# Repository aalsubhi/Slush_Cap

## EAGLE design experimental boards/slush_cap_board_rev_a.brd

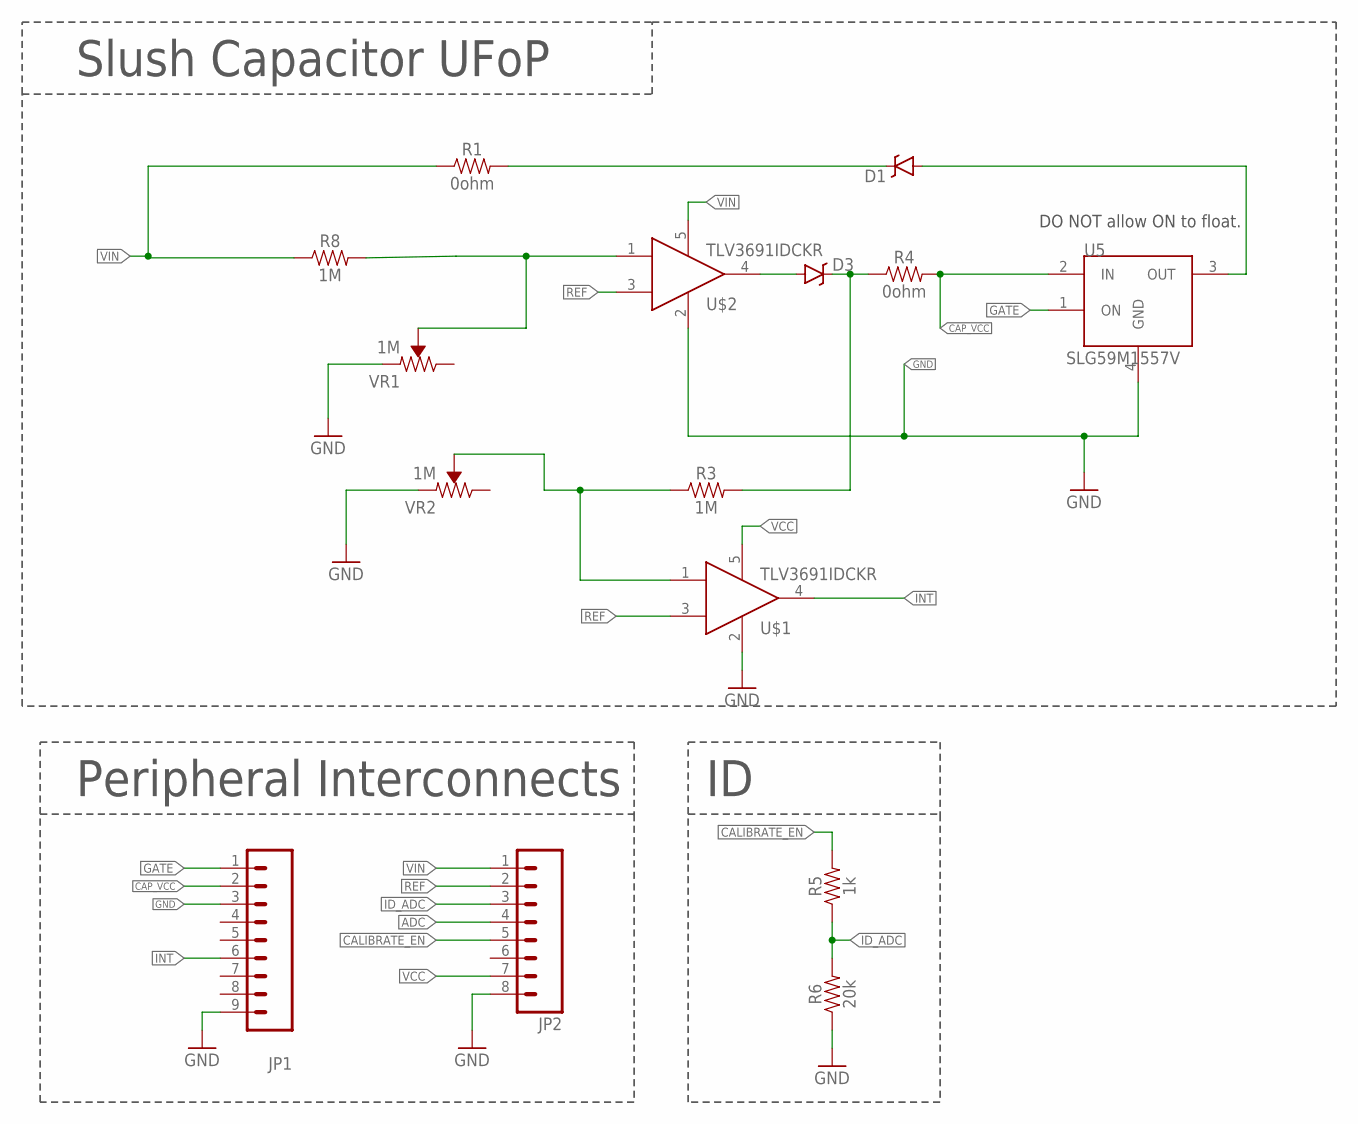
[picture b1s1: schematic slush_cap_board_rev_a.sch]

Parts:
D1, D3: RB751; SOD-523; MPN BAS40-02V-V-G-08; DIGIKEY BAS40-02V-V-G-08GICT-ND
JP1: M091.27MM; 1X09-1.27MM; MANUFACTURERPARTNUMBER GRPB091VWVN-RC; DIGIKEY S9014E-09-ND
JP2: M081.27MM; 1X08-1.27MM; MANUFACTURERPARTNUMBER GRPB081VWVN-RC; DIGIKEY S9014E-08-ND
R1, R4: 0ohm; 0603
R3, R8: 1M; 0805
R5: 1k; 0603
R6: 20k; 0603
U5: SLG59M1557V; 4STDFN; MPN SLG59M1557V; MOUSER 402-SLG59M1557V
U$1, U$2: TLV3691IDCKR; SOT353
VR1, VR2: 1M; TRIMPOT-SMD-3MM-CLOSED

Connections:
ADC: JP2.4
CALIBRATE_EN: JP2.5, R5.2
CAP_VCC: JP1.2, R4.2, U5.2 (IN)
GATE: JP1.1, U5.1 (ON)
GND: JP1.3, JP1.9, JP2.8, R6.1, U5.4 (GND), U$1.2, U$2.2, VR1.1 (CCW), VR2.1 (CCW)
ID_ADC: JP2.3, R5.1, R6.2
INT: JP1.6, U$1.4
unnamed: D3.A, U$2.4
unnamed: D3.C, R3.2, R4.1
unnamed: D1.A, U5.3 (OUT)
unnamed: R8.2, U$2.1, VR1.2 (WIPER)
unnamed: R3.1, U$1.1, VR2.2 (WIPER)
unnamed: D1.C, R1.2
REF: JP2.2, U$1.3, U$2.3
VCC: JP2.7, U$1.5
VIN: JP2.1, R1.1, R8.1, U$2.5

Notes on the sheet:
DO NOT allow ON to float.
Peripheral Interconnects
Slush Capacitor UFoP

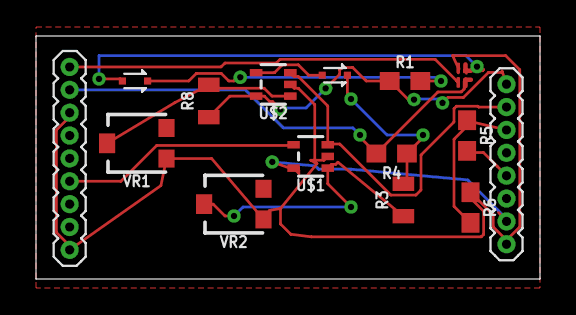
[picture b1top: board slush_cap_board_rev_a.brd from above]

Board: 2 copper layers, 28.0 x 13.5 mm, 15 parts (0 on the bottom side), 15 nets.

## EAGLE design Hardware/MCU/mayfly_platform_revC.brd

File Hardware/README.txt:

hardwareCtrl: Currently I'm using the hardware control version of the slush cap.

peripheral_platform: has the design of all peripherals that used in slush cap experiment such as radio, one analog sensor, and two analog sensors.

MCU: has Flicker board design with the extra standard headers.

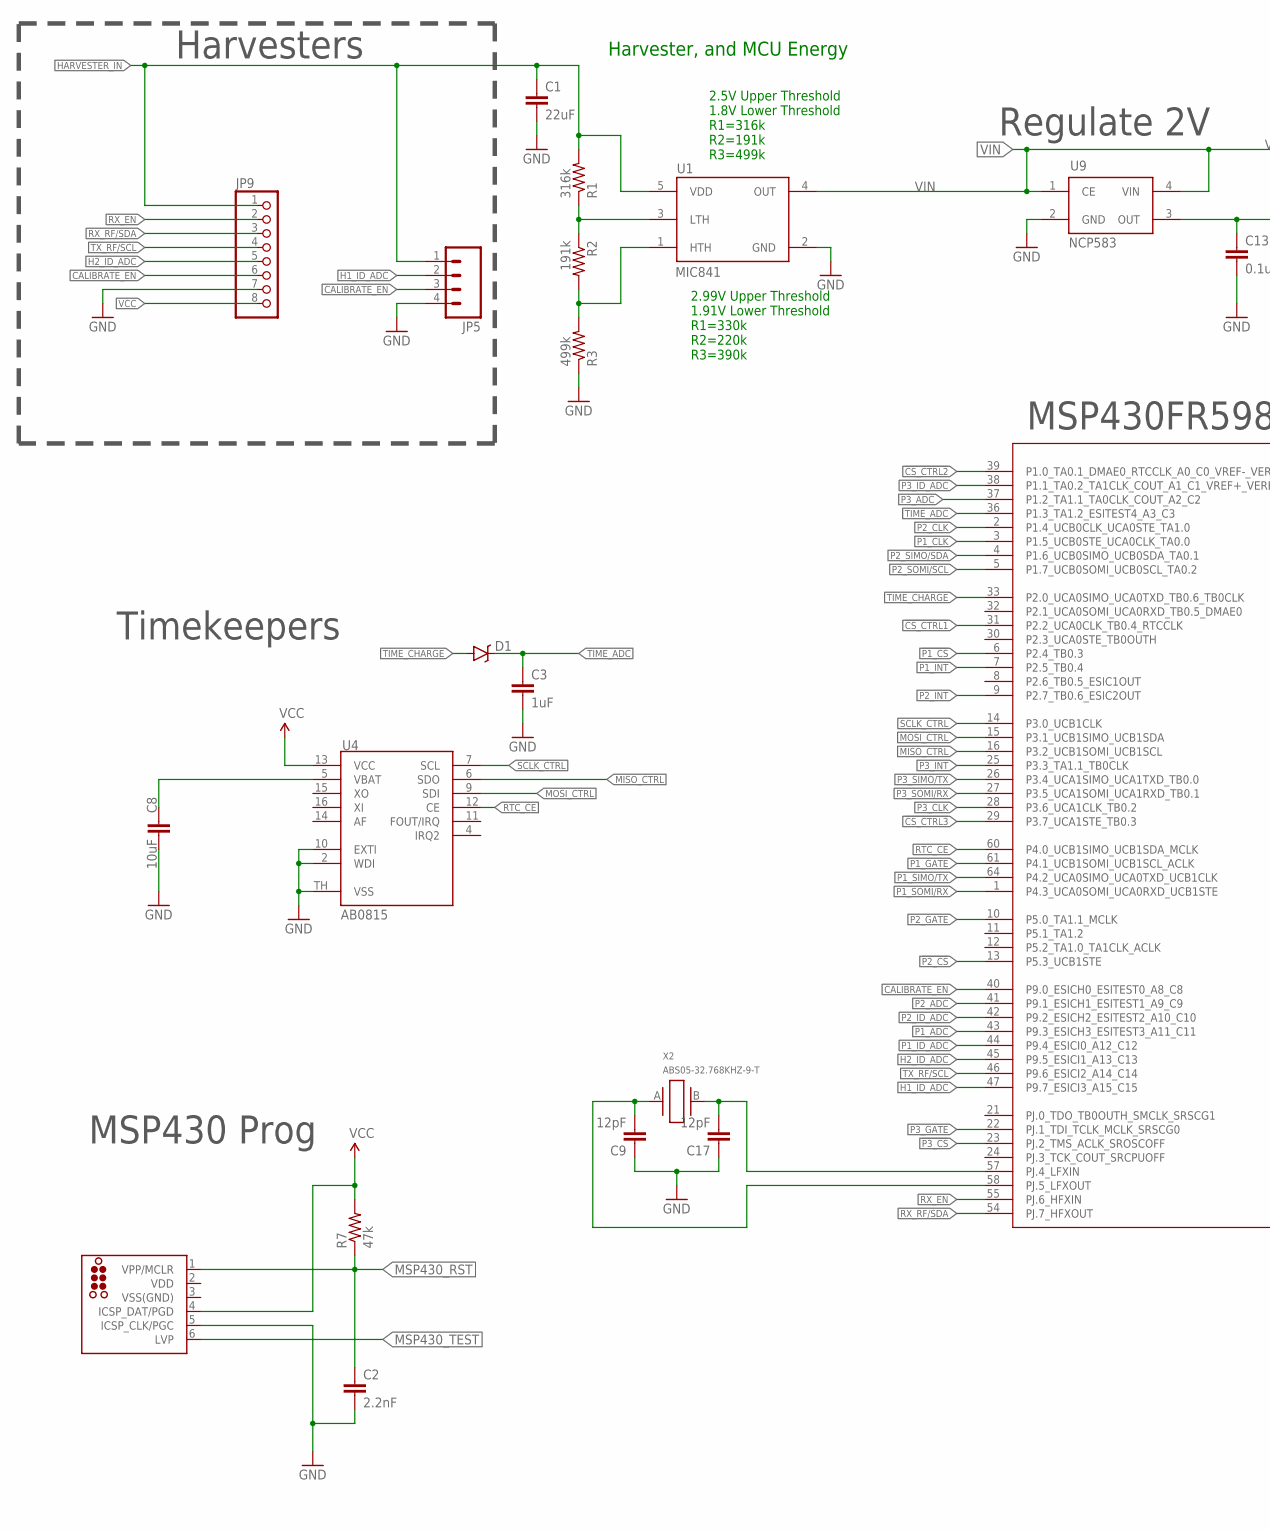
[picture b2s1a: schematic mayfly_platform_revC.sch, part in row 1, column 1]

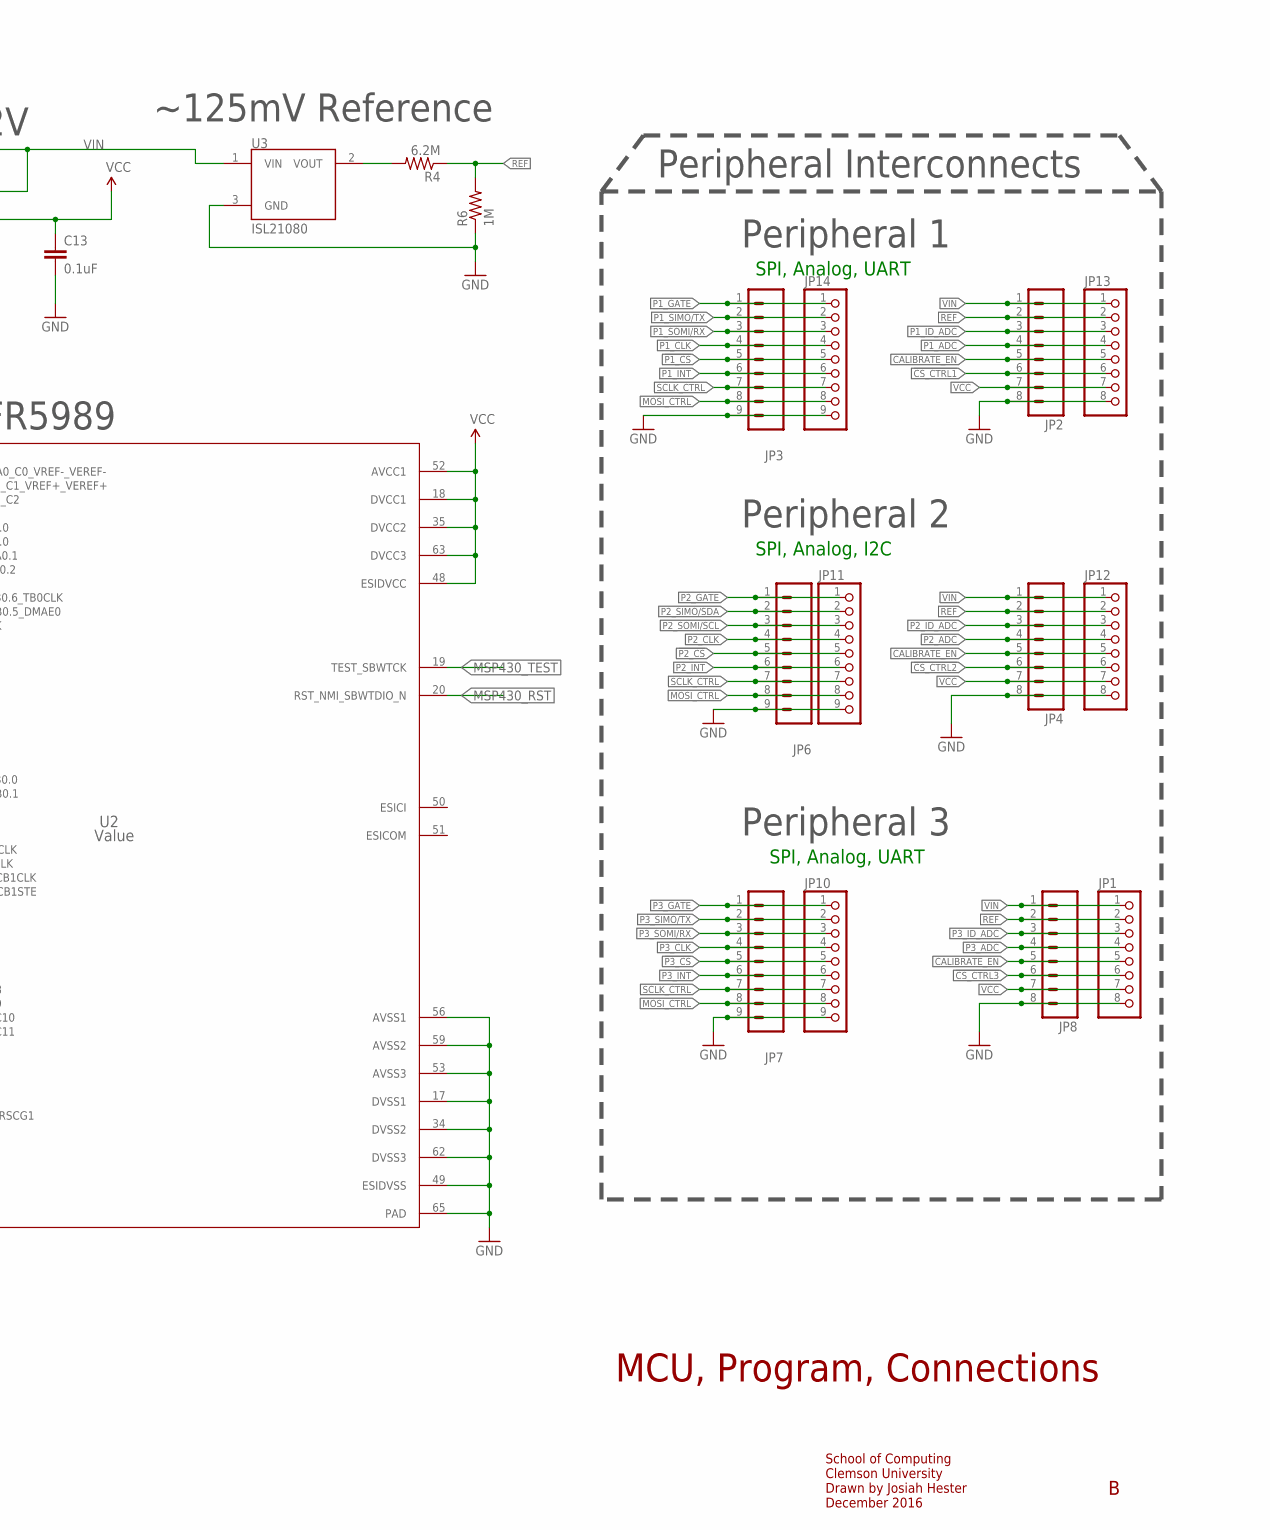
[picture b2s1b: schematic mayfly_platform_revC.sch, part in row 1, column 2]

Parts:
C1: 22uF; 1210; MANUFACTURERPARTNUMBER CL32A226KAJNNNE
C2: 2.2nF; 0603; MPN 06035C222KAT2A
C3: 1uF; 0603; MANUFACTURERPARTNUMBER 0603YD105KAT2A
C8: 10uF; 0805; MPN 0805YD106KAT2A
C9, C17: 12pF; 0603; MPN CL10C120JB8NNNC
C13: 0.1uF; 0603; MANUFACTURERPARTNUMBER 0603YC104KAT2A
D1: RB751; SOD-523; MPN BAS40-02V-V-G-08; DIGIKEY BAS40-02V-V-G-08GICT-ND
J1: TC2030-MCP-NL
JP1, JP9, JP12, JP13: PINHD-1X8; 1X08
JP2, JP4, JP8: M081.27MM; 1X08-1.27MM; MPN 851-43-008-10-001000; DIGIKEY ED90570-ND
JP3, JP6, JP7: M091.27MM; 1X09-1.27MM; MPN 851-87-009-10-001101; DIGIKEY 1212-1354-ND
JP5: M041.27MM; 1X04-1.27MM; MANUFACTURERPARTNUMBER 851-43-004-10-001000; DIGIKEY ED90528-ND
JP10, JP11, JP14: PINHD-1X9; 1X09
R1: 316k; 0603; MANUFACTURERPARTNUMBER RC0603FR-07316KL; DIGIKEY 311-316KHRCT-ND
R2: 191k; 0603; MANUFACTURERPARTNUMBER RC0603FR-07191KL; DIGIKEY 311-191KHRCT-ND
R3: 499k; 0603; MANUFACTURERPARTNUMBER RC0603FR-07499KL; DIGIKEY 311-499KHRCT-ND
R4: 6.2M; 0603; MPN CRCW06036M20FKEA; DIGIKEY 541-6.20MHCT-ND
R6: 1M; 0603; MPN RC0603FR-071ML; DIGIKEY 311-1.00MHRCT-ND
R7: 47k; 0603; MPN CRCW060347K0JNEA
U1: MIC841; SC70-5; MPN MIC841HYC5-TR; DIGIKEY 576-2923-1-ND
U2: Value; RGC0064B; MPN MSP430FR59891IRGCT; DIGIKEY 296-42031-1-ND
U3: ISL21080; SOT-23; MPN ISL21080DIH309Z-TK; DIGIKEY ISL21080DIH309Z-TKCT-ND
U4: AB0815; QFN16; MPN AB0815-T3
U9: NCP583; SC82-AB_1PRIMARY; MPN NCP583SQ18T1G; DIGIKEY NCP583SQ18T1GOSCT-ND
X2: ABS05-32.768KHZ-9-T; ABS05; MPN ABS05-32.768KHZ-9-T

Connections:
!CS_CTRL1: JP2.6, JP13.6, U2.31 (P2.2_UCA0CLK_TB0.4_RTCCLK)
!CS_CTRL2: JP4.6, JP12.6, U2.39 (P1.0_TA0.1_DMAE0_RTCCLK_A0_C0_VREF-_VER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)
!CS_CTRL3: JP1.6, JP8.6, U2.29 (P3.7_UCA1STE_TB0.3)
!P1_CS: JP3.5, JP14.5, U2.6 (P2.4_TB0.3)
!P2_CS: JP6.5, JP11.5, U2.13 (P5.3_UCB1STE)
!P3_CS: JP7.5, JP10.5, U2.23 (PJ.2_TMS_ACLK_SROSCOFF)
CALIBRATE_EN: JP1.5, JP2.5, JP4.5, JP5.3, JP8.5, JP9.6, JP12.5, JP13.5, U2.40 (P9.0_ESICH0_ESITEST0_A8_C8)
GND: C1.2, C2.2, C3.2, C8.2, C9.1, C13.2, C17.1, J1.5 (ICSP_CLK/PGC), JP1.8, JP2.8, JP3.9, JP4.8, JP5.4, JP6.9, JP7.9, JP8.8, JP9.7, JP10.9, JP11.9, JP12.8, JP13.8, JP14.9, R3.1, R6.1, U1.2 (GND), U2.17 (DVSS1), U2.34 (DVSS2), U2.49 (ESIDVSS), U2.53 (AVSS3), U2.56 (AVSS1), U2.59 (AVSS2), U2.62 (DVSS3), U2.65 (PAD), U3.3 (GND), U4.2 (WDI), U4.10 (EXTI), U4.TH (VSS), U9.2 (GND)
H1_ID_ADC: JP5.2, U2.47 (P9.7_ESICI3_A15_C15)
H2_ID_ADC: JP9.5, U2.45 (P9.5_ESICI1_A13_C13)
HARVESTER_IN: C1.1, JP5.1, JP9.1, R1.2, U1.5 (VDD)
MISO_CTRL: U2.16 (P3.2_UCB1SOMI_UCB1SCL), U4.6 (SDO)
MOSI_CTRL: JP3.8, JP6.8, JP7.8, JP10.8, JP11.8, JP14.8, U2.15 (P3.1_UCB1SIMO_UCB1SDA), U4.9 (SDI)
MSP430_RST: C2.1, J1.1 (VPP/MCLR), R7.1, U2.20 (RST_NMI_SBWTDIO_N)
MSP430_TEST: J1.6 (LVP), U2.19 (TEST_SBWTCK)
unnamed: R1.1, R2.1, U1.3 (LTH)
unnamed: R4.2, U3.2 (VOUT)
unnamed: R2.2, R3.2, U1.1 (HTH)
unnamed: C17.2, U2.57 (PJ.4_LFXIN), X2.B (2)
unnamed: C9.2, U2.58 (PJ.5_LFXOUT), X2.A (1)
unnamed: C8.1, U4.5 (VBAT)
P1_ADC: JP2.4, JP13.4, U2.43 (P9.3_ESICH3_ESITEST3_A11_C11)
P1_CLK: JP3.4, JP14.4, U2.3 (P1.5_UCB0STE_UCA0CLK_TA0.0)
P1_GATE: JP3.1, JP14.1, U2.61 (P4.1_UCB1SOMI_UCB1SCL_ACLK)
P1_ID_ADC: JP2.3, JP13.3, U2.44 (P9.4_ESICI0_A12_C12)
P1_INT: JP3.6, JP14.6, U2.7 (P2.5_TB0.4)
P1_SIMO/TX: JP3.2, JP14.2, U2.64 (P4.2_UCA0SIMO_UCA0TXD_UCB1CLK)
P1_SOMI/RX: JP3.3, JP14.3, U2.1 (P4.3_UCA0SOMI_UCA0RXD_UCB1STE)
P2_ADC: JP4.4, JP12.4, U2.41 (P9.1_ESICH1_ESITEST1_A9_C9)
P2_CLK: JP6.4, JP11.4, U2.2 (P1.4_UCB0CLK_UCA0STE_TA1.0)
P2_GATE: JP6.1, JP11.1, U2.10 (P5.0_TA1.1_MCLK)
P2_ID_ADC: JP4.3, JP12.3, U2.42 (P9.2_ESICH2_ESITEST2_A10_C10)
P2_INT: JP6.6, JP11.6, U2.9 (P2.7_TB0.6_ESIC2OUT)
P2_SIMO/SDA: JP6.2, JP11.2, U2.4 (P1.6_UCB0SIMO_UCB0SDA_TA0.1)
P2_SOMI/SCL: JP6.3, JP11.3, U2.5 (P1.7_UCB0SOMI_UCB0SCL_TA0.2)
P3_ADC: JP1.4, JP8.4, U2.37 (P1.2_TA1.1_TA0CLK_COUT_A2_C2)
P3_CLK: JP7.4, JP10.4, U2.28 (P3.6_UCA1CLK_TB0.2)
P3_GATE: JP7.1, JP10.1, U2.22 (PJ.1_TDI_TCLK_MCLK_SRSCG0)
P3_ID_ADC: JP1.3, JP8.3, U2.38 (P1.1_TA0.2_TA1CLK_COUT_A1_C1_VREF+_VERE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)
P3_INT: JP7.6, JP10.6, U2.25 (P3.3_TA1.1_TB0CLK)
P3_SIMO/TX: JP7.2, JP10.2, U2.26 (P3.4_UCA1SIMO_UCA1TXD_TB0.0)
P3_SOMI/RX: JP7.3, JP10.3, U2.27 (P3.5_UCA1SOMI_UCA1RXD_TB0.1)
REF: JP1.2, JP2.2, JP4.2, JP8.2, JP12.2, JP13.2, R4.1, R6.2
RTC_CE: U2.60 (P4.0_UCB1SIMO_UCB1SDA_MCLK), U4.12 (CE)
RX_EN: JP9.2, U2.55 (PJ.6_HFXIN)
RX_RF/SDA: JP9.3, U2.54 (PJ.7_HFXOUT)
SCLK_CTRL: JP3.7, JP6.7, JP7.7, JP10.7, JP11.7, JP14.7, U2.14 (P3.0_UCB1CLK), U4.7 (SCL)
TIME_ADC: C3.1, D1.C, U2.36 (P1.3_TA1.2_ESITEST4_A3_C3)
TIME_CHARGE: D1.A, U2.33 (P2.0_UCA0SIMO_UCA0TXD_TB0.6_TB0CLK)
TX_RF/SCL: JP9.4, U2.46 (P9.6_ESICI2_A14_C14)
VCC: C13.1, J1.4 (ICSP_DAT/PGD), JP1.7, JP2.7, JP4.7, JP8.7, JP9.8, JP12.7, JP13.7, R7.2, U2.18 (DVCC1), U2.35 (DVCC2), U2.48 (ESIDVCC), U2.52 (AVCC1), U2.63 (DVCC3), U4.13 (VCC), U9.3 (OUT)
VDD: J1.2 (VDD)
VIN: JP1.1, JP2.1, JP4.1, JP8.1, JP12.1, JP13.1, U1.4 (OUT), U3.1 (VIN), U9.1 (CE), U9.4 (VIN)
VSS(GND): J1.3 (VSS(GND))

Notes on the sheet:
MCU, Program, Connections
School of Computing Clemson University Drawn by Josiah Hester December 2016
MSP430FR5989
Regulate 2V
MSP430 Prog
Timekeepers
2.99V Upper Threshold 1.91V Lower Threshold R1=330k R2=220k R3=390k
Harvester, and MCU Energy
~125mV Reference
Peripheral 1
Peripheral 2
Peripheral 3
Harvesters
SPI, Analog, I2C
SPI, Analog, UART
Peripheral Interconnects
2.5V Upper Threshold 1.8V Lower Threshold R1=316k R2=191k R3=499k

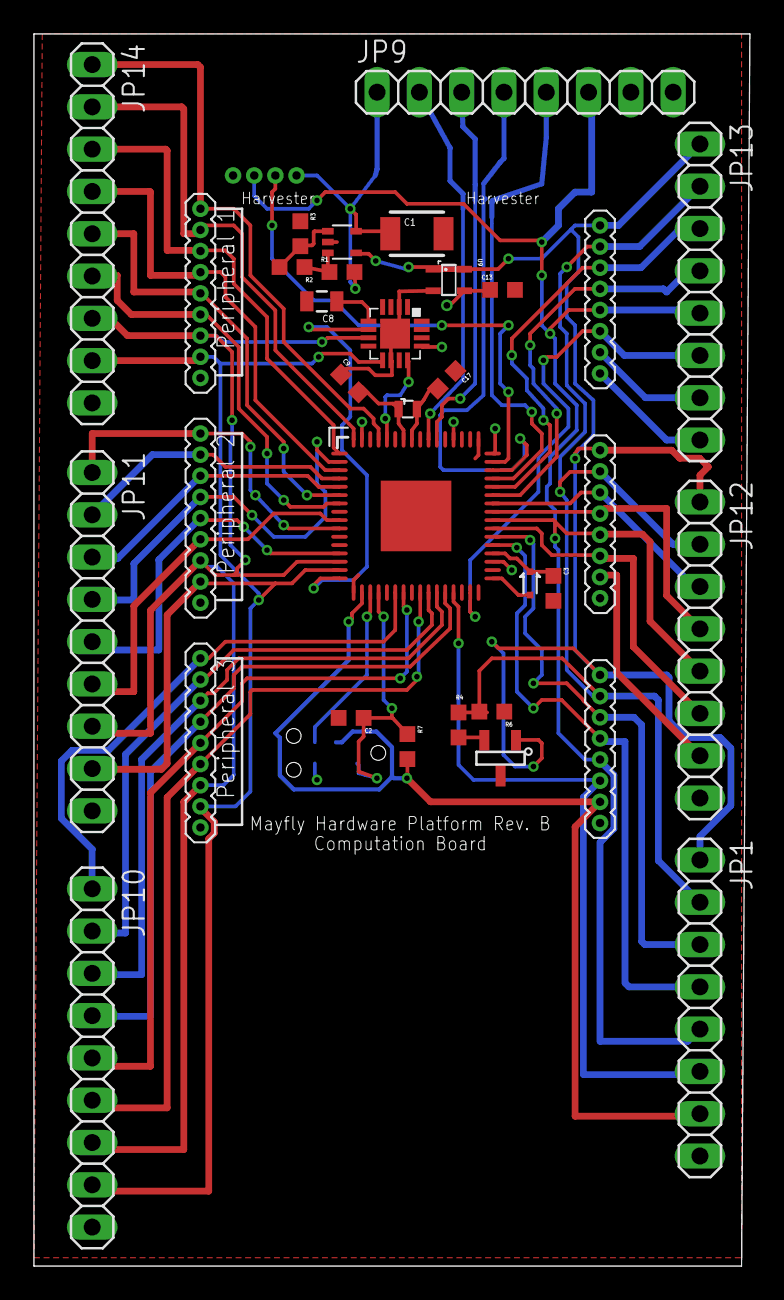
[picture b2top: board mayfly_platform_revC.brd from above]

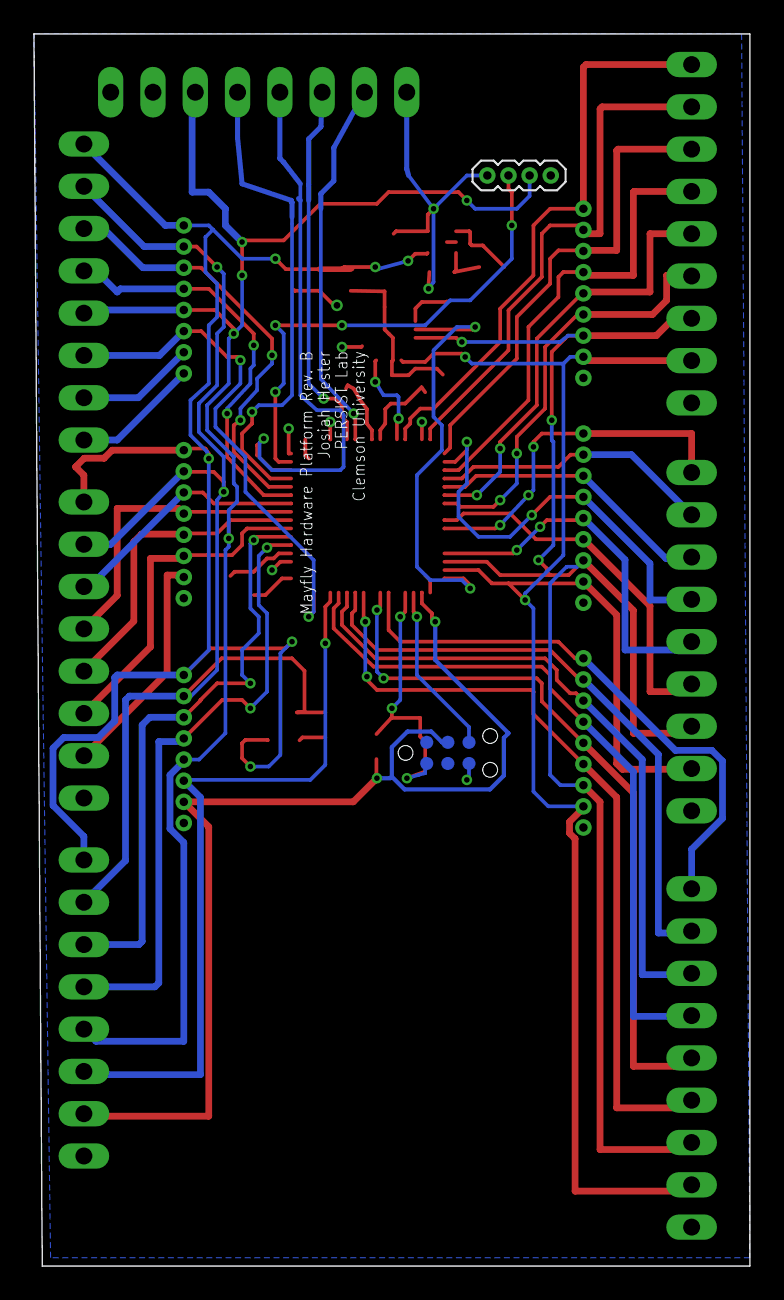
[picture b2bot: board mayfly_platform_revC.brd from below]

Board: 2 copper layers, 43.0 x 74.0 mm, 35 parts (2 on the bottom side), 52 nets.

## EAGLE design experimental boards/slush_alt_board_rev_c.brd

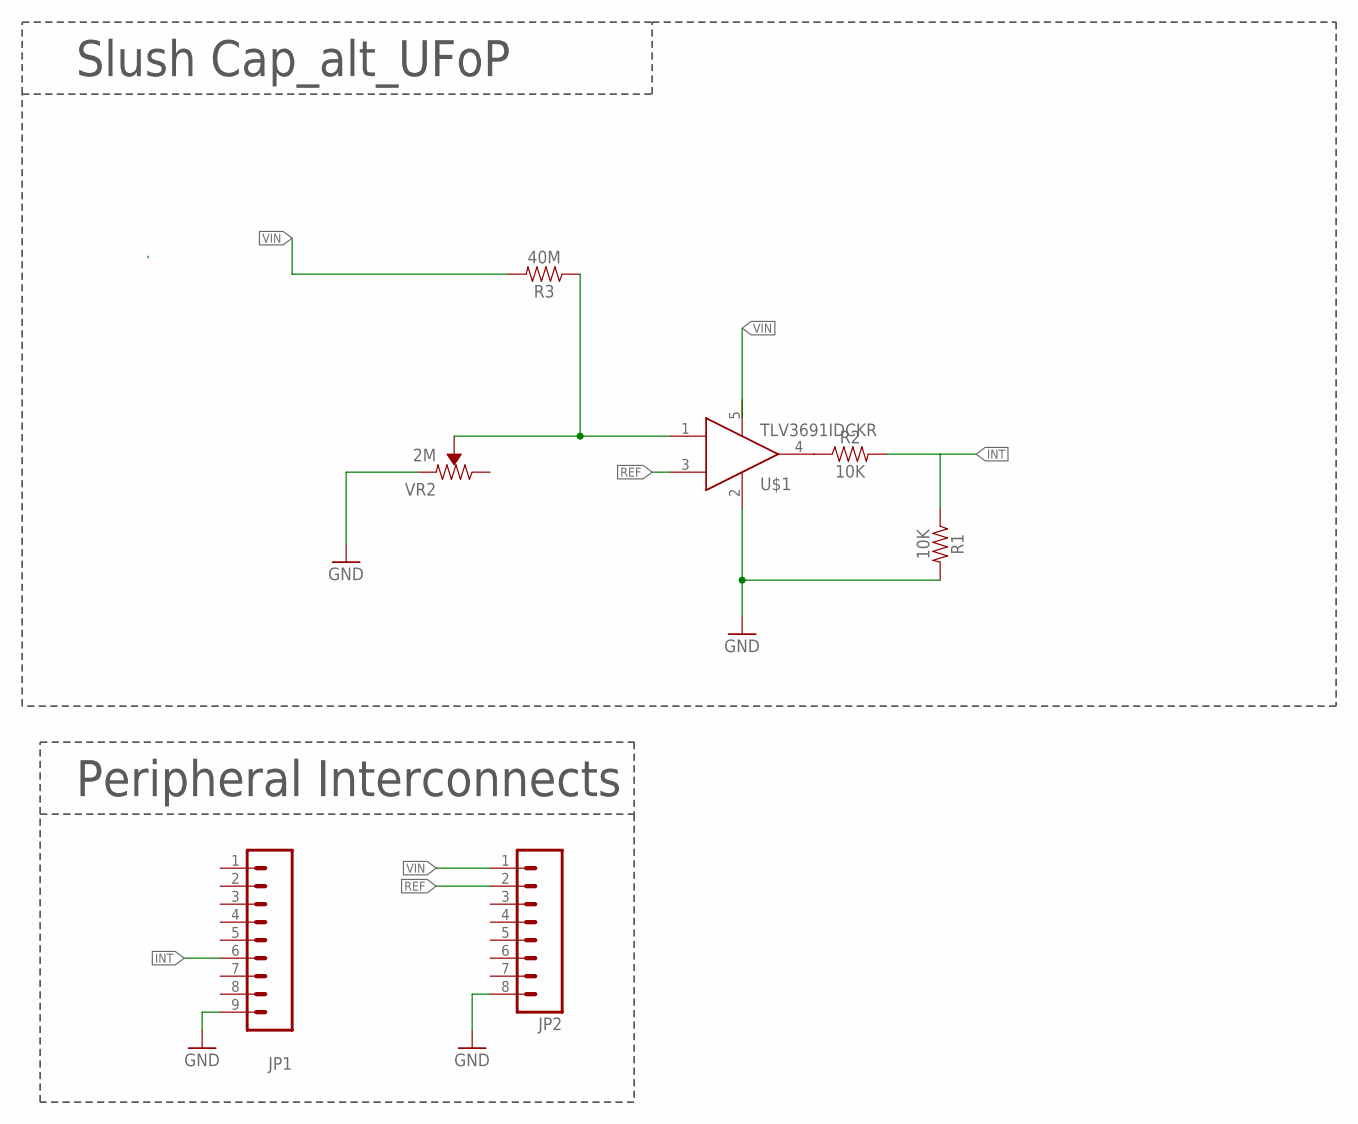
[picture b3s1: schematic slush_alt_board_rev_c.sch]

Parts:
JP1: M091.27MM; 1X09-1.27MM; MANUFACTURERPARTNUMBER GRPB091VWVN-RC; DIGIKEY S9014E-09-ND
JP2: M081.27MM; 1X08-1.27MM; MANUFACTURERPARTNUMBER GRPB081VWVN-RC; DIGIKEY S9014E-08-ND
R1, R2: 10K; 0805
R3: 40M; 0805
U$1: TLV3691IDCKR; SOT353
VR2: 2M; TRIMPOT-SMD-3MM-CLOSED

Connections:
GND: JP1.9, JP2.8, R1.2, U$1.2, VR2.1 (CCW)
INT: JP1.6, R1.1, R2.2
unnamed: R2.1, U$1.4
unnamed: R3.1, U$1.1, VR2.2 (WIPER)
REF: JP2.2, U$1.3
VIN: JP2.1, R3.2, U$1.5

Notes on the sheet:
Peripheral Interconnects
Slush Cap_alt_UFoP

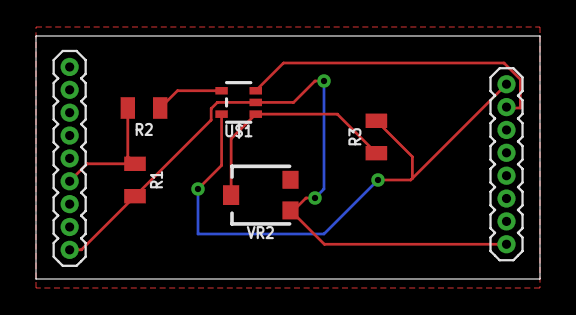
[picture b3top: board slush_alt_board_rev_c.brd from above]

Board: 2 copper layers, 28.0 x 13.5 mm, 7 parts (0 on the bottom side), 6 nets.

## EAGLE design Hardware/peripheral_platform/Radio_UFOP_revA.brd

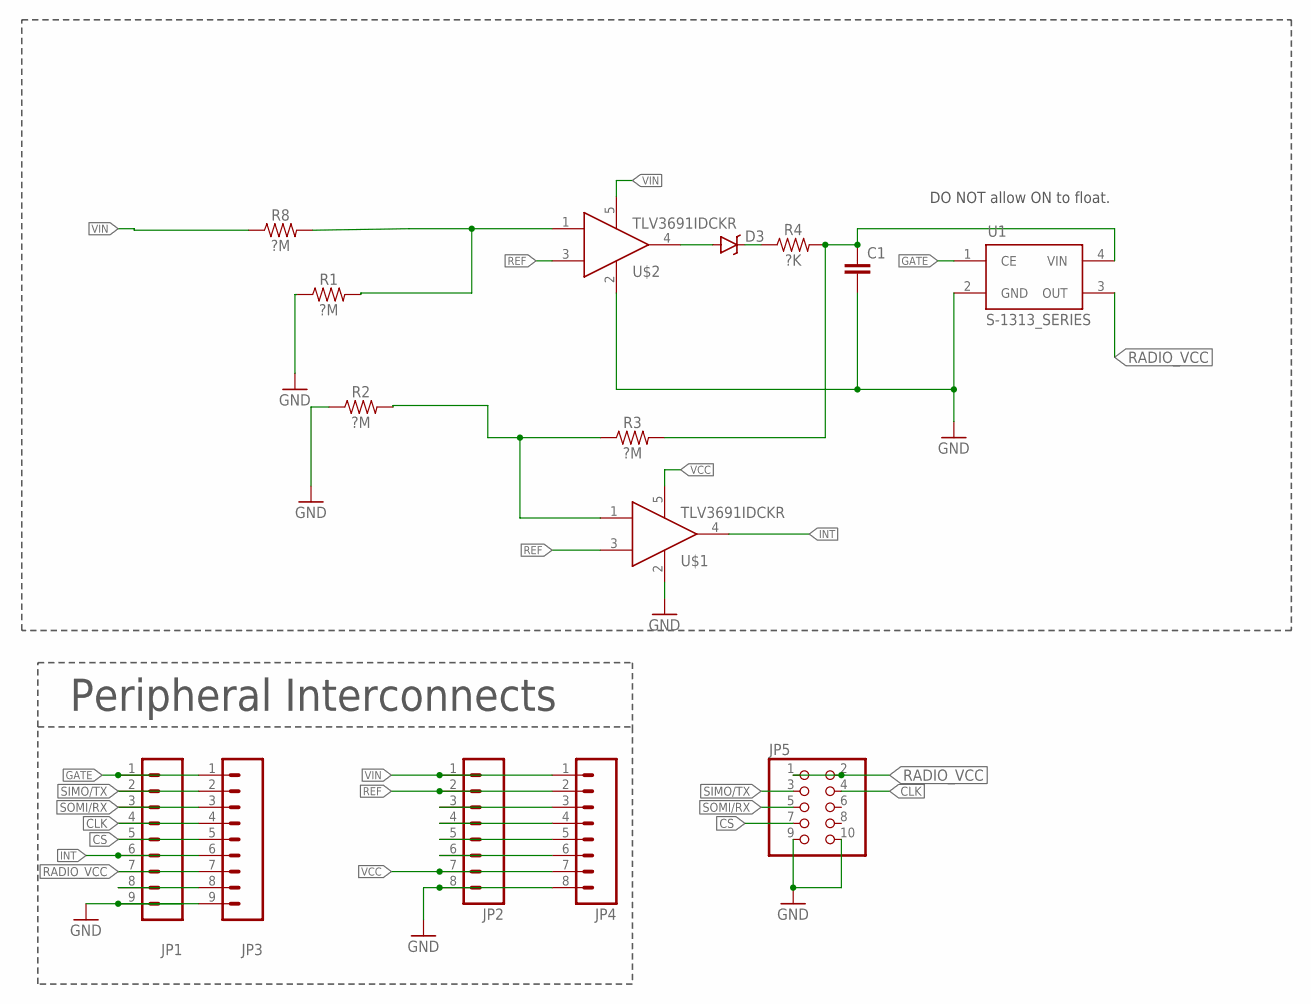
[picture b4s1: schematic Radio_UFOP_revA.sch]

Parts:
C1: CAP0603-CAP; 0603-CAP
D3: RB751; SOD-523; MPN BAS40-02V-V-G-08; DIGIKEY BAS40-02V-V-G-08GICT-ND
JP1, JP3: M091.27MM; 1X09-1.27MM; MANUFACTURERPARTNUMBER GRPB091VWVN-RC; DIGIKEY S9014E-09-ND
JP2, JP4: M081.27MM; 1X08-1.27MM; MANUFACTURERPARTNUMBER GRPB081VWVN-RC; DIGIKEY S9014E-08-ND
JP5: PINHD-2X5; 2X05
R1, R2, R3, R8: ?M; 0805
R4: ?K; 0805
U1: S-1313_SERIES; SC82-AB_1PRIMARY
U$1, U$2: TLV3691IDCKR; SOT353

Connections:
CLK: JP1.4, JP3.4, JP5.4
CS: JP1.5, JP3.5, JP5.7
GATE: JP1.1, JP3.1, U1.1 (CE)
GND: C1.2, JP1.9, JP2.8, JP3.9, JP4.8, JP5.9, JP5.10, R1.1, R2.1, U1.2 (GND), U$1.2, U$2.2
INT: JP1.6, JP3.6, U$1.4
unnamed: D3.A, U$2.4
unnamed: R1.2, R8.2, U$2.1
unnamed: R2.2, R3.1, U$1.1
unnamed: D3.C, R4.1
unnamed: JP1.8, JP3.8
unnamed: JP2.6, JP4.6
unnamed: JP2.5, JP4.5
unnamed: JP2.4, JP4.4
unnamed: JP2.3, JP4.3
unnamed: C1.1, R3.2, R4.2, U1.4 (VIN)
RADIO_VCC: JP1.7, JP3.7, JP5.1, JP5.2, U1.3 (OUT)
REF: JP2.2, JP4.2, U$1.3, U$2.3
SIMO/TX: JP1.2, JP3.2, JP5.3
SOMI/RX: JP1.3, JP3.3, JP5.5
VCC: JP2.7, JP4.7, U$1.5
VIN: JP2.1, JP4.1, R8.1, U$2.5

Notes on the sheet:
DO NOT allow ON to float.
Peripheral Interconnects

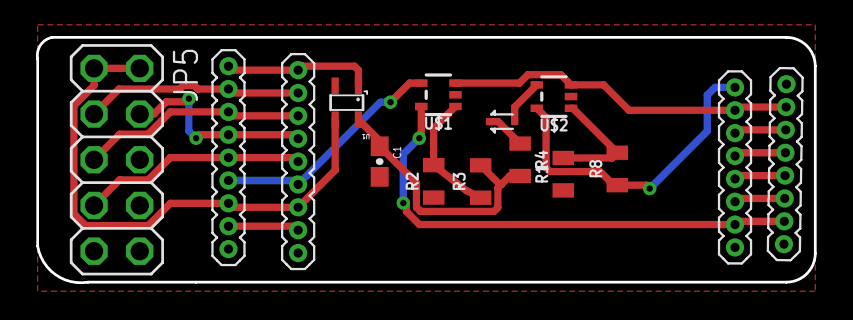
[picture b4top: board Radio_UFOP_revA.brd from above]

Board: 2 copper layers, 43.2 x 13.6 mm, 15 parts (0 on the bottom side), 21 nets.

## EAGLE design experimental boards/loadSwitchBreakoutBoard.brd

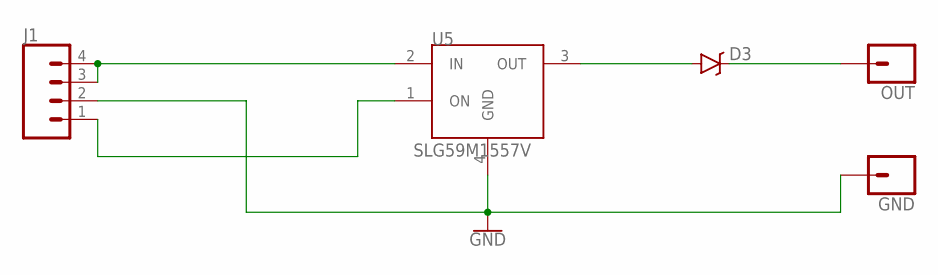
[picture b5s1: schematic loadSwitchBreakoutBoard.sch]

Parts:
D3: RB751; SOD-523; MPN BAS40-02V-V-G-08; DIGIKEY BAS40-02V-V-G-08GICT-ND
GND: CONN_01; 1X01
J1: CONN_04; 1X04
OUT: CONN_01; 1X01
U5: SLG59M1557V; 4STDFN; MPN SLG59M1557V; MOUSER 402-SLG59M1557V

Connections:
GND: GND.1, J1.2, U5.4 (GND)
IN: J1.3, J1.4, U5.2 (IN)
unnamed: D3.A, U5.3 (OUT)
unnamed: D3.C, OUT.1
ON: J1.1, U5.1 (ON)

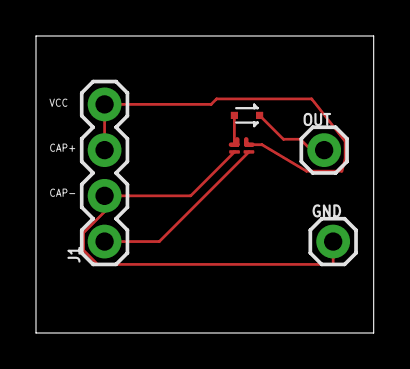
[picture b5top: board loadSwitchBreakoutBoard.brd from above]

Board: 2 copper layers, 18.8 x 16.5 mm, 5 parts (0 on the bottom side), 5 nets.

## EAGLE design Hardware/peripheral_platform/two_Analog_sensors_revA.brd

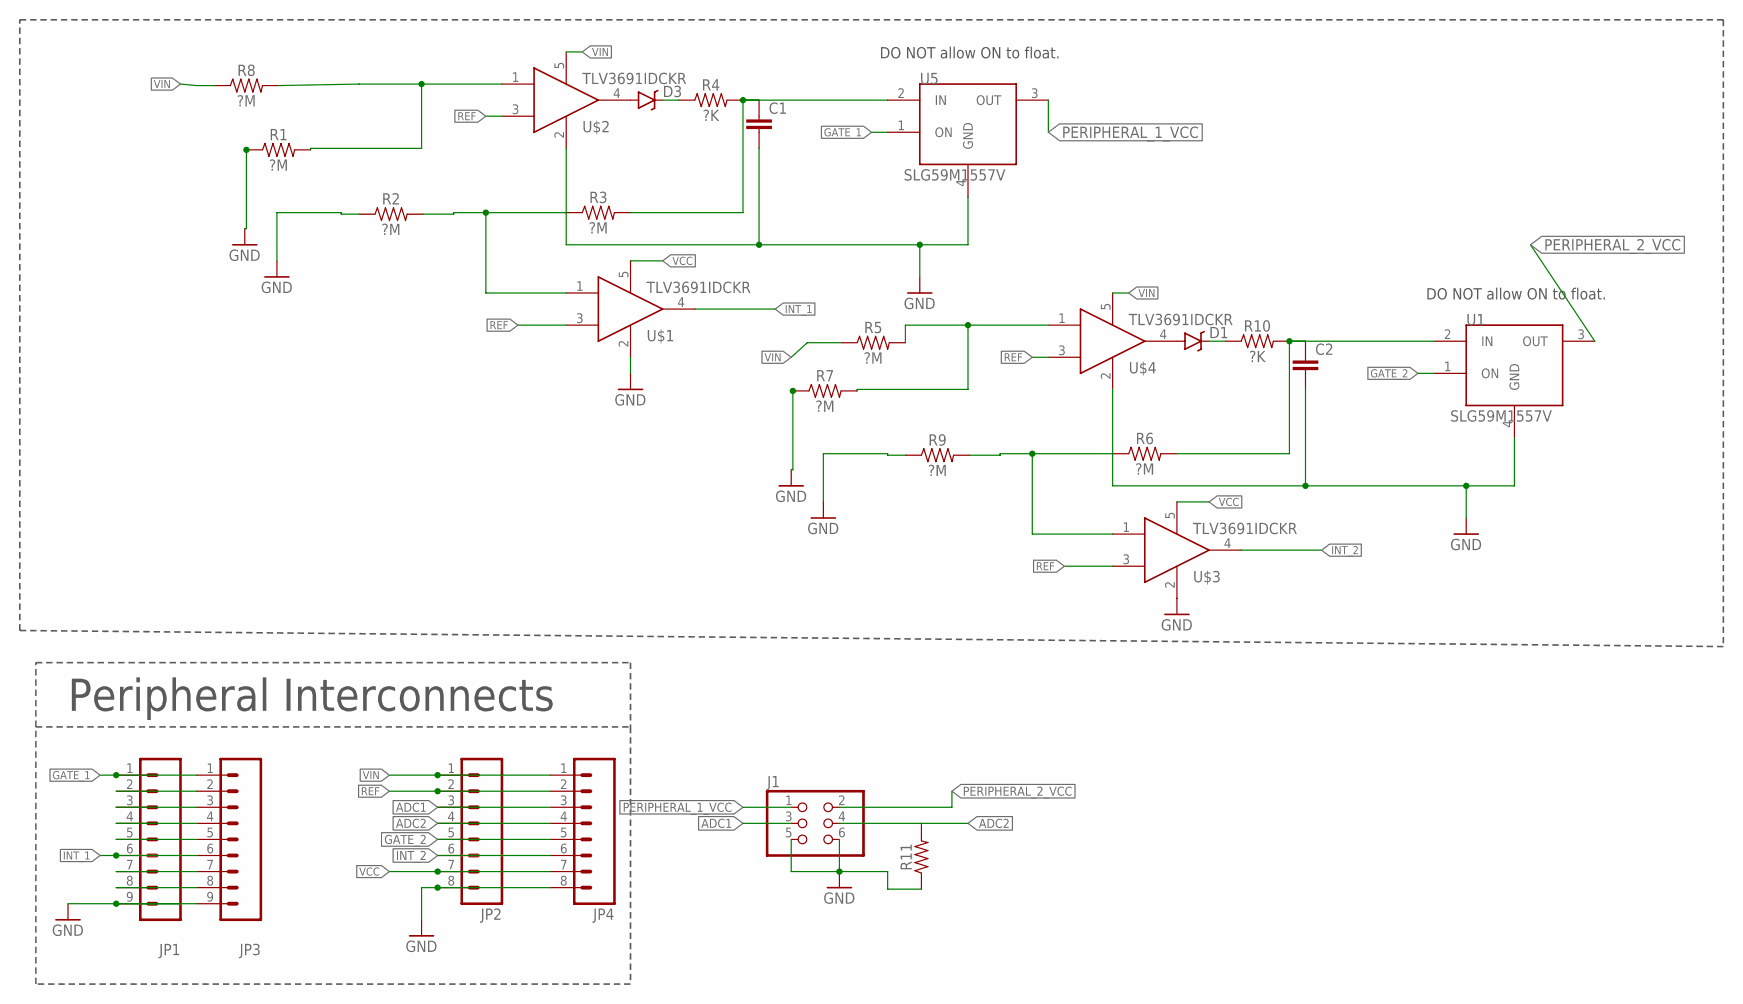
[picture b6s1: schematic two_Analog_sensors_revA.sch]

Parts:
C1, C2: CAP0603-CAP; 0603-CAP
D1, D3: RB751; SOD-523; MPN BAS40-02V-V-G-08; DIGIKEY BAS40-02V-V-G-08GICT-ND
J1: PINHD-2X3; 2X03
JP1, JP3: M091.27MM; 1X09-1.27MM; MANUFACTURERPARTNUMBER GRPB091VWVN-RC; DIGIKEY S9014E-09-ND
JP2, JP4: M081.27MM; 1X08-1.27MM; MANUFACTURERPARTNUMBER GRPB081VWVN-RC; DIGIKEY S9014E-08-ND
R1, R2, R3, R5, R6, R7, R8, R9: ?M; 0805
R4, R10: ?K; 0805
R11: 0.3OHM-0805-1/8W-1%; 0805
U1, U5: SLG59M1557V; 4STDFN; MPN SLG59M1557V; MOUSER 402-SLG59M1557V
U$1, U$2, U$3, U$4: TLV3691IDCKR; SOT353

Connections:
ADC1: J1.3, JP2.3, JP4.3
ADC2: J1.4, JP2.4, JP4.4, R11.2
GATE_1: JP1.1, JP3.1, U5.1 (ON)
GATE_2: JP2.5, JP4.5, U1.1 (ON)
GND: C1.2, C2.2, J1.5, J1.6, JP1.9, JP2.8, JP3.9, JP4.8, R1.1, R2.1, R7.1, R9.1, R11.1, U1.4 (GND), U5.4 (GND), U$1.2, U$2.2, U$3.2, U$4.2
INT_1: JP1.6, JP3.6, U$1.4
INT_2: JP2.6, JP4.6, U$3.4
unnamed: D3.A, U$2.4
unnamed: JP1.4, JP3.4
unnamed: JP1.2, JP3.2
unnamed: R1.2, R8.2, U$2.1
unnamed: R2.2, R3.1, U$1.1
unnamed: JP1.5, JP3.5
unnamed: JP1.7, JP3.7
unnamed: JP1.8, JP3.8
unnamed: R5.2, R7.2, U$4.1
unnamed: JP1.3, JP3.3
unnamed: R6.1, R9.2, U$3.1
unnamed: D3.C, R4.1
unnamed: D1.A, U$4.4
unnamed: D1.C, R10.1
unnamed: C2.1, R6.2, R10.2, U1.2 (IN)
unnamed: C1.1, R3.2, R4.2, U5.2 (IN)
PERIPHERAL_1_VCC: J1.1, U5.3 (OUT)
PERIPHERAL_2_VCC: J1.2, U1.3 (OUT)
REF: JP2.2, JP4.2, U$1.3, U$2.3, U$3.3, U$4.3
VCC: JP2.7, JP4.7, U$1.5, U$3.5
VIN: JP2.1, JP4.1, R5.1, R8.1, U$2.5, U$4.5

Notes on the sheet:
DO NOT allow ON to float.
Peripheral Interconnects

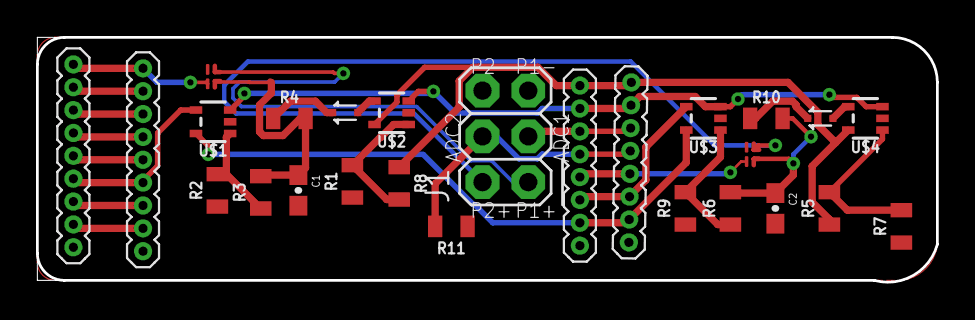
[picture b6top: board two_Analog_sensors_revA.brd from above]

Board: 2 copper layers, 50.0 x 13.6 mm, 26 parts (0 on the bottom side), 28 nets.

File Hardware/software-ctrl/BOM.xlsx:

Part | Value | Package | Description | MOUSER#
D1 | RB751 | SOD-523 | Schottky diodes | 78-BAS40-02V-V-G-08
D3 | RB751 | SOD-523 | Schottky diodes | 78-BAS40-02V-V-G-08
JP1 |  | 1X09-1.27MM | Header 9
JP2 |  | 1X08-1.27MM | Header 8
R1 | 0ohm | 603 | resistor
R2 | 100M(1%or5%) | 805 | resistor
R3 | 100M(1%or5%) | 805 | resistor
R4 | 0ohm | 603 | resistor
R7 | 100M(1%or5%) | 805 | resistor
R8 | 40M | 805 | resistor
R9 | 100M(1%or5%) | 805 | resistor
U$1 | TLV3691IDCKR | SOT353 | comparetor | 595-TLV3691IDCKR
U$2 | TLV3691IDCKR | SOT353 | comparetor | 595-TLV3691IDCKR
U5 | SLG59M1557V | 4STDFN | power switch | 402-SLG59M1557V
VR1 | 2M | TRIMPOT-SMD-3MM-CLOSED | Trimming Potentiometer (Trimpot) | 652-3313J-1-205E

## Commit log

2018-10-26 updating the repo
2018-10-27 fixing app2
2018-10-30 cleaning up the app2 code

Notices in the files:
parts and their libraries:
SparkFun-Capacitors: Licensing: Creative Commons ShareAlike 4.0 International - https://creativecommons.org/licenses/by-sa/4.0
tag-connect_msp430: ©2009 ROFA.cz - modified and updated by Robert Darlington ‹rdarlington@gmail.com›
